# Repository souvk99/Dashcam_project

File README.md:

# Dashcam Prototype Project

A full-stack dashcam prototype built from scratch, covering mechanical design, hardware, software, and documentation.

## Project Structure

```
Dashcam_project/
├── mechanicals/        # CAD models, enclosure, mounts, and physical design
│   ├── source/         # Original design files (CAD, STL, STEP, etc.)
│   └── simulation/     # Structural / thermal simulations
├── hardware/           # PCB schematics, circuit design, component selection
│   ├── source/         # KiCad / Eagle / Altium design files
│   └── simulation/     # SPICE and circuit simulations
├── software/           # Firmware and application code
│   ├── source/         # Production source code
│   └── simulation/     # Software-in-the-loop / emulation scripts
└── documentation/      # Datasheets, design decisions, user guides, reports
```

## Project Goals

- [ ] Design a compact dashcam enclosure
- [ ] Select and integrate camera, storage, and power hardware
- [ ] Develop firmware for video capture, loop recording, and event detection
- [ ] Validate design through simulation before prototyping
- [ ] Produce complete documentation for reproducibility

## Getting Started

Refer to each subfolder's `README.md` for domain-specific instructions and toolchain requirements.

## License

TBD

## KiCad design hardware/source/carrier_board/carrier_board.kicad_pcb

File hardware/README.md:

# Hardware

This folder contains all electronic hardware design assets for the dashcam prototype.

## Structure

| Folder | Contents |
|--------|----------|
| `source/` | Schematics, PCB layout files, BOM (Bill of Materials), Gerber files, wiring diagrams |
| `simulation/` | SPICE simulations, signal integrity analysis, power analysis |

## Recommended Tools

- **Schematic / PCB**: KiCad / EasyEDA / Altium Designer
- **SPICE Simulation**: LTspice / Ngspice
- **Component Research**: Octopart / DigiKey / Mouser / Robu.in

## Selected System Components

- **Core SBC**: Luckfox Pico Mini B (RV1103 SoC, 64MB DDR2, 128MB SPI NAND)
- **Camera Module**: SmartSens SC3336 3MP MIPI CSI-2 (98.3° wide-angle lens)
- **Onboard Storage**: 128MB SPI NAND Flash (zero external SD card required)
- **Wireless Interface**: Realtek RTL8188EUS USB 802.11n Wi-Fi Dongle (SoftAP RTSP streaming)
- **Battery & PMIC**: 3.7V 1000mAh LiPo Battery (PCM protected) + IP5306 Synchronous PMIC (load-sharing)
- **Vehicle Pre-Regulator**: LM2596 DC-DC Step-Down Buck (12V to 5.0V DC)
- **Transient Protection**: SMBJ5.0A TVS diode, 470µF bulk electrolytic capacitors, 100nF ceramic decoupling

## Design Considerations

- Automotive 12V transient overvoltage protection (clamping up to 40V spikes)
- Low-power operation (~2.66W active streaming)
- Multi-stage decoupling and anti-sleep keep-alive circuit for the PMIC

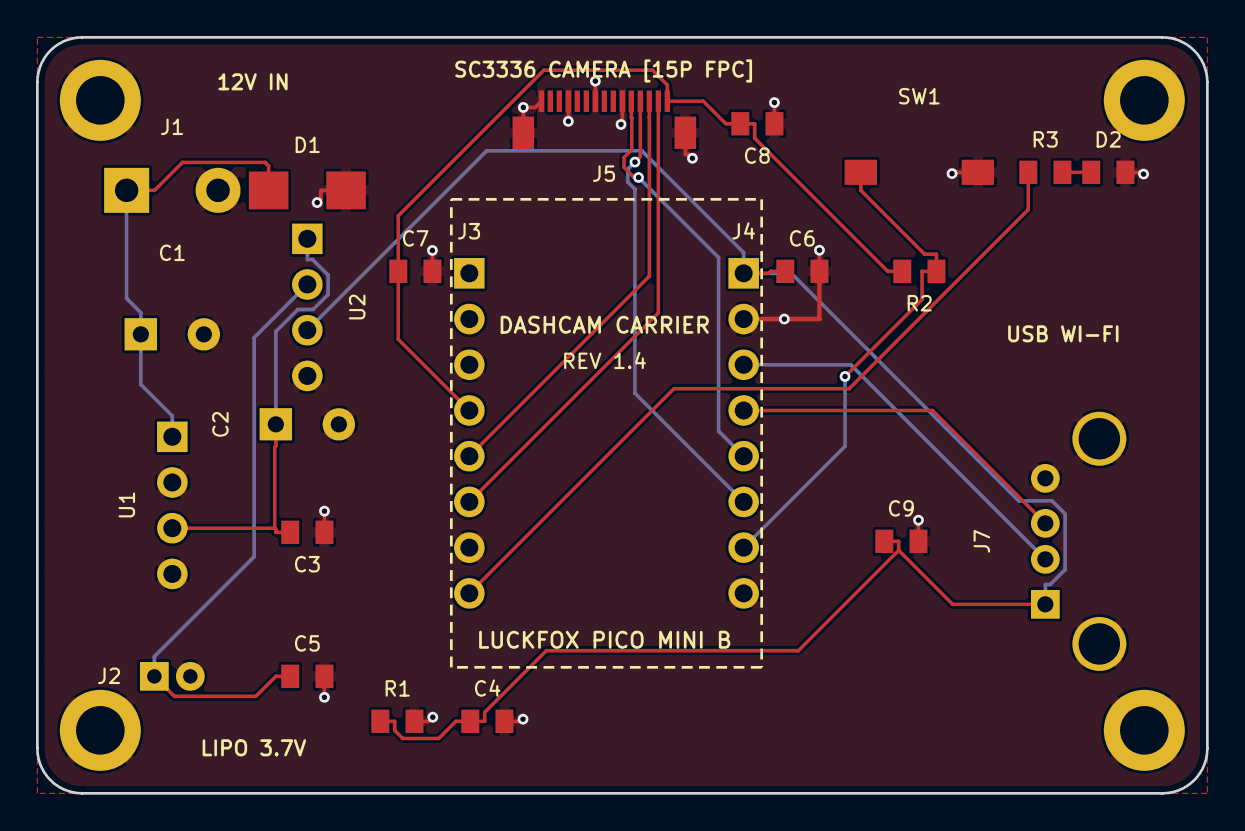
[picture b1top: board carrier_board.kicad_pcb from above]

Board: 2 copper layers, 65.0 x 42.0 mm, 23 parts (0 on the bottom side), 15 nets.

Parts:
C1, C2: 470uF; CP_Radial_D8.0mm_P3.50mm
C3, C4, C5, C6, C7, C8, C9: 100nF; C_0805_2012Metric
D1: SMBJ5.0A; D_SMB
D2: STAT_LED; LED_0805_2012Metric
J1: 12V_IN; TerminalBlock_bornier-2_P5.08mm
J2: LIPO_BAT; JST_PH_S2B-PH-K_1x02_P2.00mm_Horizontal
J3: LUCKFOX_J1; PinSocket_1x08_P2.54mm_Vertical
J4: LUCKFOX_J2; PinSocket_1x08_P2.54mm_Vertical
J5: SC3336_FPC; Hirose_FH12-15S-0.5SH_1x15-1MP_P0.50mm_Horizontal
J7: USB_WIFI; USB_A_Molex_67643_Horizontal
R1: 100R; R_0805_2012Metric
R2: 10k; R_0805_2012Metric
R3: 470R; R_0805_2012Metric
SW1: PWR_BTN; SW_Push_1P1T_NO_6x6mm_H9.5mm
U1: LM2596_BUCK; PinHeader_1x04_P2.54mm_Vertical
U2: IP5306_BMS; PinHeader_1x04_P2.54mm_Vertical

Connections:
+3V3: C7.1, C8.1, J3.4, J5.15, R2.1
+5V_PRE: C2.1, C3.1, U1.3, U2.1
+5V_SYS: C4.1, C6.1, C9.1, J4.1, J7.1, R1.1, U2.3
+12V: C1.1, D1.1, J1.1, U1.1
CAM_PDN: J4.6, J5.12
CAM_RSTn: J4.5, J5.11
GND: C1.2, C2.2, C3.2, C4.2, C5.2, C6.2, C7.2, C8.2, C9.2, D1.2, D2.2, J1.2, J2.2, J3.3, J3.7, J4.2, J4.8, J5.1, J5.4, J5.7, J5.10, J5.MP1, J5.MP2, J7.4, J7.SH, R1.2, SW1.2, U1.2, U1.4, U2.4
I2C3_SCL: J3.5, J5.13
I2C3_SDA: J3.6, J5.14
unnamed: D2.1, R3.2
STAT_LED: J3.8, R3.1
SW_SENSE: J4.7, R2.2, SW1.1
USB_DM: J4.3, J7.2
USB_DP: J4.4, J7.3
VBAT: C5.1, J2.1, U2.2

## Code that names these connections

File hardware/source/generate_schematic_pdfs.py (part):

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          │ VCC (3.3V, Pin 8) ──► 100nF │  MIPI_D1_N ─────┼─► Pin 8: MIPI_RX_D1_N (Lane 1 -)  │
          │ GND (Pin 4)                 │  MIPI_D1_P ─────┼─► Pin 9: MIPI_RX_D1_P (Lane 1 +)  │
          └─────────────────────────────┘                 │ Pin 10: GND                     │
                                                   GPIO   │ Pin 11: CAM_RSTn (Sensor Reset) │
          USB 2.0 HIGH-SPEED HOST PORT             GPIO   │ Pin 12: CAM_PDN (Power Down)    │
          ┌─────────────────────────────┐        I2C_SCL ─┼─► Pin 13: I2C3_SCL (SCCB Clock) │
RV1103    │ Pin 1: VBUS (+5.0V DC)      │        I2C_SDA ─┼─► Pin 14: I2C3_SDA (SCCB Data)  │
USB_DM  ──┼─► Pin 2: Data Negative (D-) │                 │ Pin 15: VCC_3V3 (Sensor Power)  │
USB_DP  ──┼─► Pin 3: Data Positive (D+) │                 └─────────────────────────────────┘
          │ Pin 4: GND (System Ground)  │
          └─────────────────────────────┘</div>

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
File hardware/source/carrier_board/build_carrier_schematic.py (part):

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    sb.add_power_symbol("GND", 80.0, 252.0)
    sb.add_wire(80.0, 247.81, 80.0, 252.0) # C9 Pin 2

    # J7 Pin 2 USB_DM & Pin 3 USB_DP
    sb.add_wire(56.92, 246.54, 28.0, 246.54)
    sb.add_label("USB_DM", 28.0, 246.54, justify="left bottom")

    sb.add_wire(56.92, 249.08, 28.0, 249.08)
    sb.add_label("USB_DP", 28.0, 249.08, justify="left bottom")

    # J7 Pin 4 GND (routed left to X=44 to clear USB_WIFI_PORT label)
    sb.add_wire(56.92, 251.62, 44.0, 251.62)
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    sb.add_junction(114.0, 252.0)
    sb.add_wire(114.0, 252.0, 122.92, 252.0) # Node right to SW1 Pin 1
    sb.add_wire(114.0, 252.0, 96.0, 252.0)   # Node left to SW_SENSE
    sb.add_label("SW_SENSE", 96.0, 252.0, justify="left bottom")

    sb.add_wire(133.08, 252.0, 138.0, 252.0)
    sb.add_wire(138.0, 252.0, 138.0, 258.0) # SW1 Pin 2 to GND
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
    sb.add_wire(160.0, 234.19, 160.0, 232.0)
    sb.add_wire(160.0, 232.0, 144.0, 232.0)
    sb.add_label("STAT_LED", 144.0, 232.0, justify="left bottom")

    sb.add_wire(160.0, 241.81, 160.0, 244.0)
    sb.add_wire(160.0, 244.0, 174.0, 244.0)
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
